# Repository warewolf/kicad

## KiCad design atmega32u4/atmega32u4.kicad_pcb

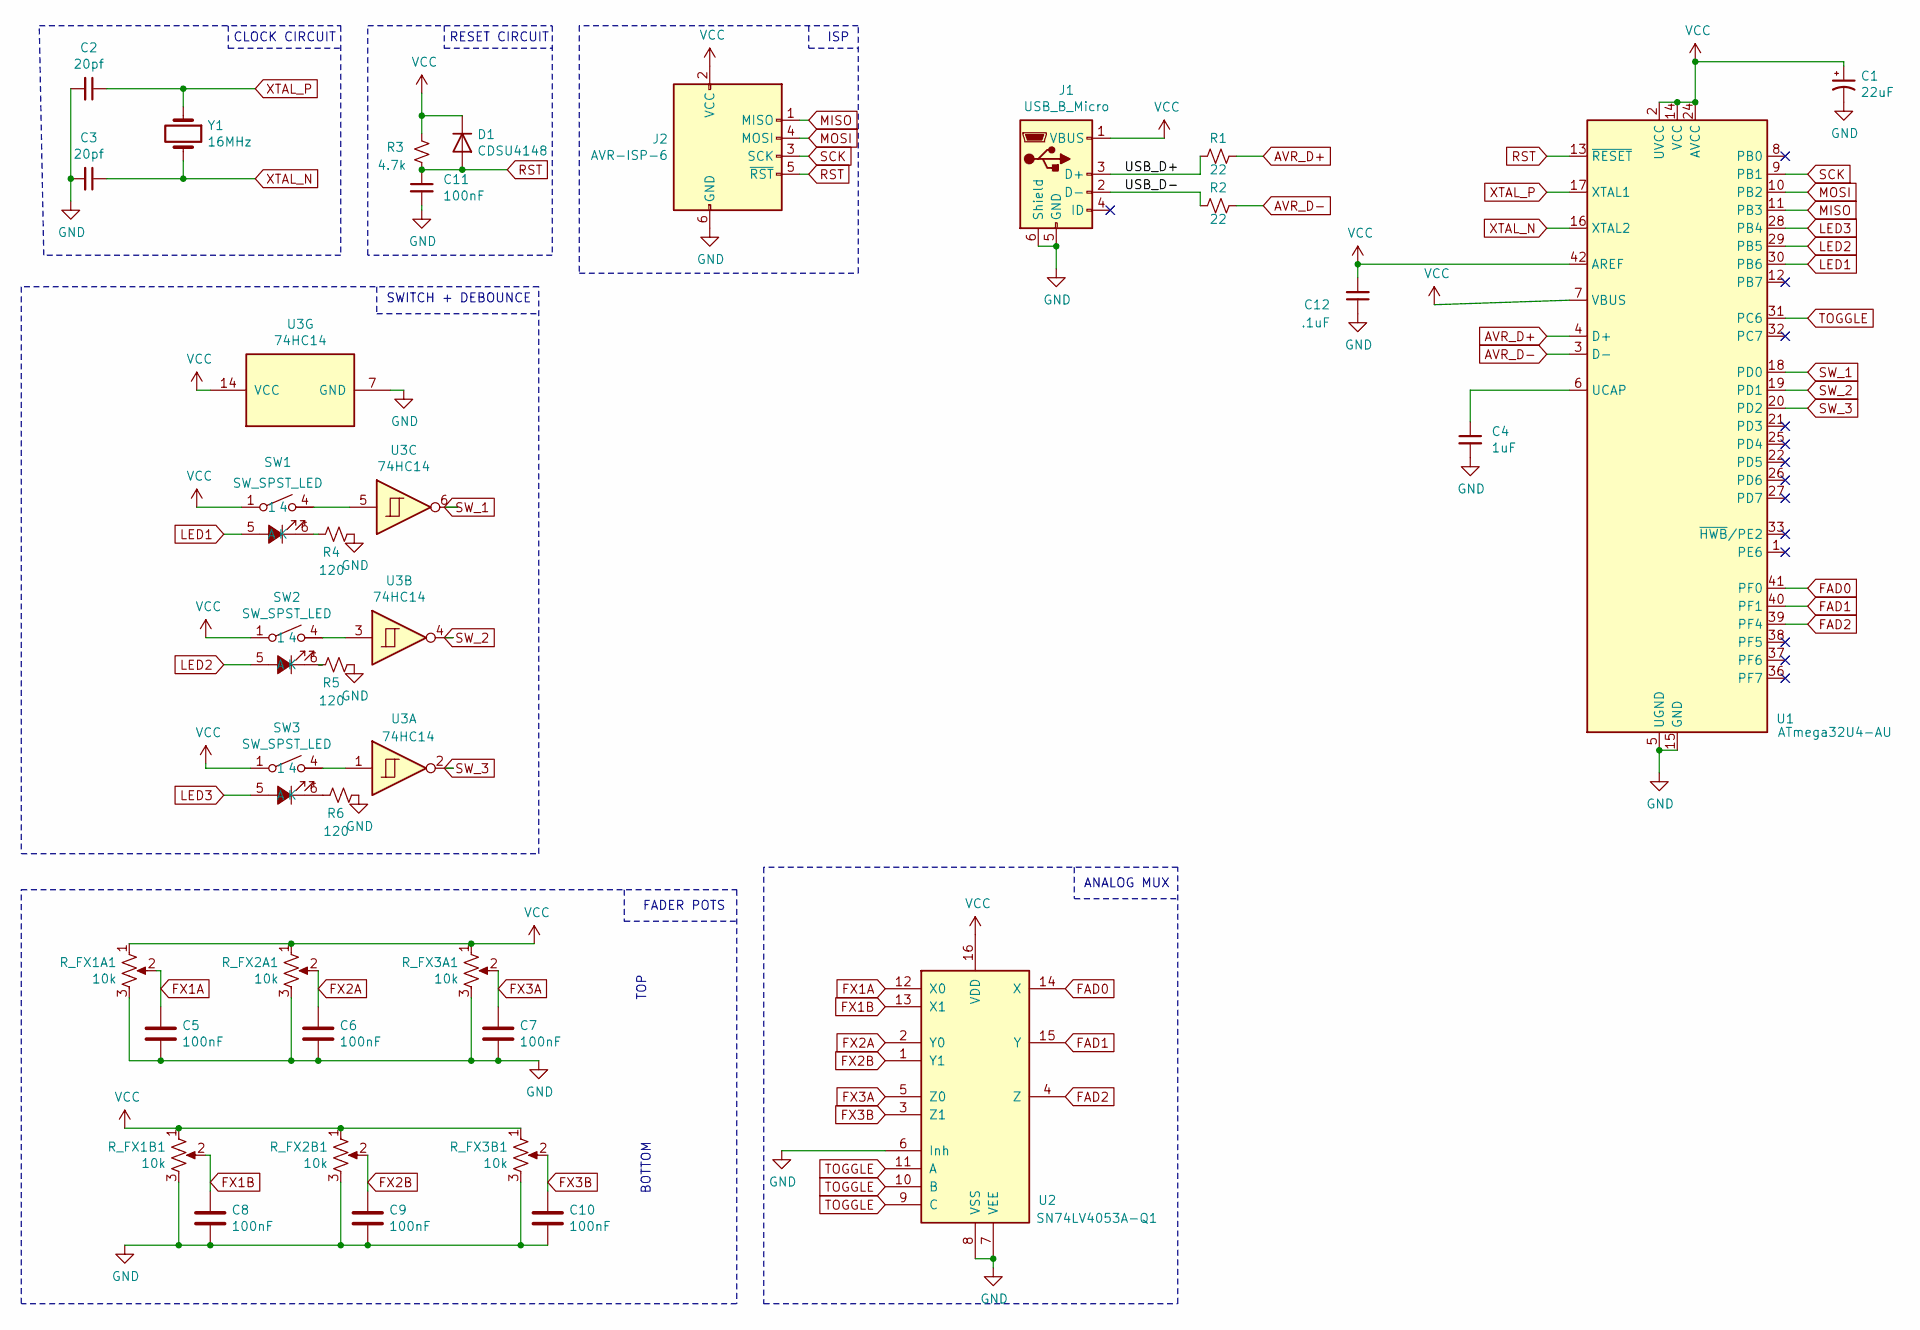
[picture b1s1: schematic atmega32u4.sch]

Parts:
C1: 22uF; CP_Radial_D4.0mm_P2.00mm
C2, C3: 20pf; C_0805_2012Metric
C4: 1uF; C_0805_2012Metric
C5, C6, C7, C8, C9, C10, C11: 100nF; C_0805_2012Metric
C12: .1uF; C_0805_2012Metric
D1: CDSU4148; D_0603_1608Metric
J1: USB_B_Micro; USB_Micro-B_Molex-105017-0001
J2: AVR-ISP-6; PinHeader_2x03_P2.54mm_Vertical
R1, R2: 22; R_0805_2012Metric
R3: 4.7k; R_0805_2012Metric
R4, R5, R6: 120; R_0805_2012Metric
R_FX1A1, R_FX1B1, R_FX2A1, R_FX2B1, R_FX3A1, R_FX3B1: 10k; Potentiometer_TT_P090S_Vertical
SW1, SW2, SW3: SW_SPST_LED; ILS TA180 10
U1: ATmega32U4-AU; TQFP-44_10x10mm_P0.8mm
U2: SN74LV4053A-Q1; TSSOP-16_4.4x5mm_P0.65mm
U3: 74HC14; TSSOP-16_4.4x5mm_P0.65mm
Y1: 16MHz; Crystal_SMD_7050-2Pin_7.0x5.0mm

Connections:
/USB_D+: J1.3 (D+), R1.2
/USB_D-: J1.2 (D-), R2.2
AVR_D+: R1.1, U1.4 (D+)
AVR_D-: R2.1, U1.3 (D-)
FAD0: U1.41 (PF0), U2.14 (X)
FAD1: U1.40 (PF1), U2.15 (Y)
FAD2: U1.39 (PF4), U2.4 (Z)
FX1A: C5.1, R_FX1A1.2, U2.12 (X0)
FX1B: C8.1, R_FX1B1.2, U2.13 (X1)
FX2A: C6.1, R_FX2A1.2, U2.2 (Y0)
FX2B: C9.1, R_FX2B1.2, U2.1 (Y1)
FX3A: C7.1, R_FX3A1.2, U2.5 (Z0)
FX3B: C10.1, R_FX3B1.2, U2.3 (Z1)
GND: C1.2, C2.2, C3.2, C4.2, C5.2, C6.2, C7.2, C8.2, C9.2, C10.2, C11.2, C12.1, J1.5 (GND), J1.6 (Shield), J2.6 (GND), R4.1, R5.1, R6.1, R_FX1A1.3, R_FX1B1.3, R_FX2A1.3, R_FX2B1.3, R_FX3A1.3, R_FX3B1.3, U1.5 (UGND), U1.15 (GND), U1.23 (GND), U1.35 (GND), U1.43 (GND), U2.6 (Inh), U2.7 (VEE), U2.8 (VSS), U3.7 (GND)
LED1: SW1.5 (A), U1.30 (PB6)
LED2: SW2.5 (A), U1.29 (PB5)
LED3: SW3.5 (A), U1.28 (PB4)
MISO: J2.1 (MISO), U1.11 (PB3)
MOSI: J2.4 (MOSI), U1.10 (PB2)
unnamed: C4.1, U1.6 (UCAP)
unnamed: R4.2, SW1.6 (K)
unnamed: R5.2, SW2.6 (K)
unnamed: R6.2, SW3.6 (K)
unnamed: SW1.3, SW1.4, U3.5
unnamed: SW2.3, SW2.4, U3.3
unnamed: SW3.3, SW3.4, U3.1
RST: C11.1, D1.2 (A), J2.5 (~RST), R3.1, U1.13 (~RESET)
SCK: J2.3 (SCK), U1.9 (PB1)
SW_1: U1.18 (PD0), U3.6
SW_2: U1.19 (PD1), U3.4
SW_3: U1.20 (PD2), U3.2
TOGGLE: U1.31 (PC6), U2.9 (C), U2.10 (B), U2.11 (A)
VCC: C1.1, C12.2, D1.1 (K), J1.1 (VBUS), J2.2 (VCC), R3.2, R_FX1A1.1, R_FX1B1.1, R_FX2A1.1, R_FX2B1.1, R_FX3A1.1, R_FX3B1.1, SW1.1, SW1.2, SW2.1, SW2.2, SW3.1, SW3.2, U1.2 (UVCC), U1.7 (VBUS), U1.14 (VCC), U1.24 (AVCC), U1.34 (VCC), U1.42 (AREF), U1.44 (AVCC), U2.16 (VDD), U3.14 (VCC)
XTAL_N: C3.1, U1.16 (XTAL2), Y1.2
XTAL_P: C2.1, U1.17 (XTAL1), Y1.1

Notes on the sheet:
RESET CIRCUIT
BOTTOM
FADER POTS
CLOCK CIRCUIT
SWITCH + DEBOUNCE
TOP
ISP
ANALOG MUX

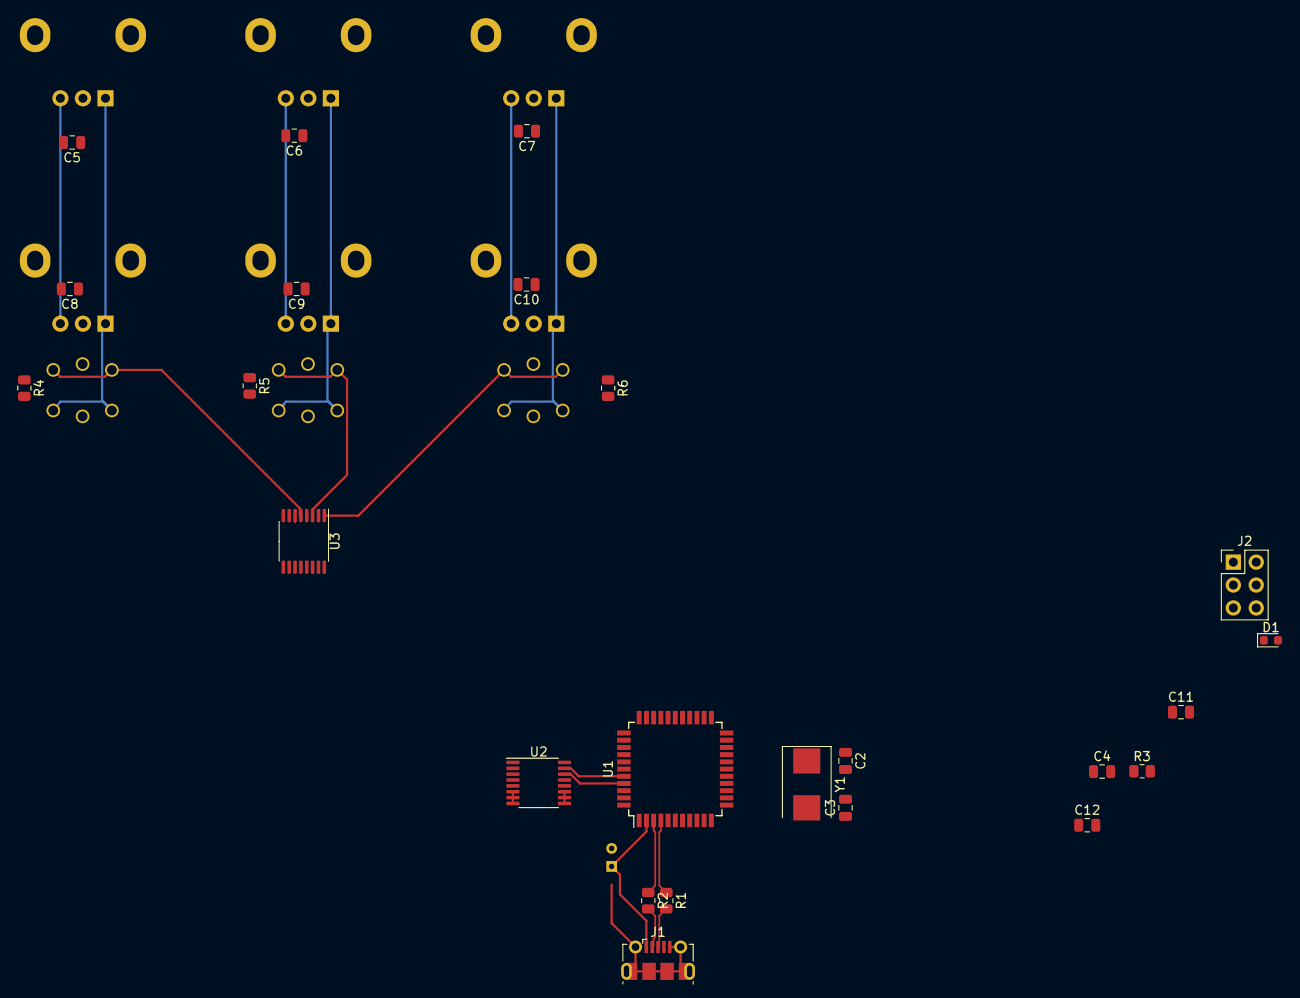
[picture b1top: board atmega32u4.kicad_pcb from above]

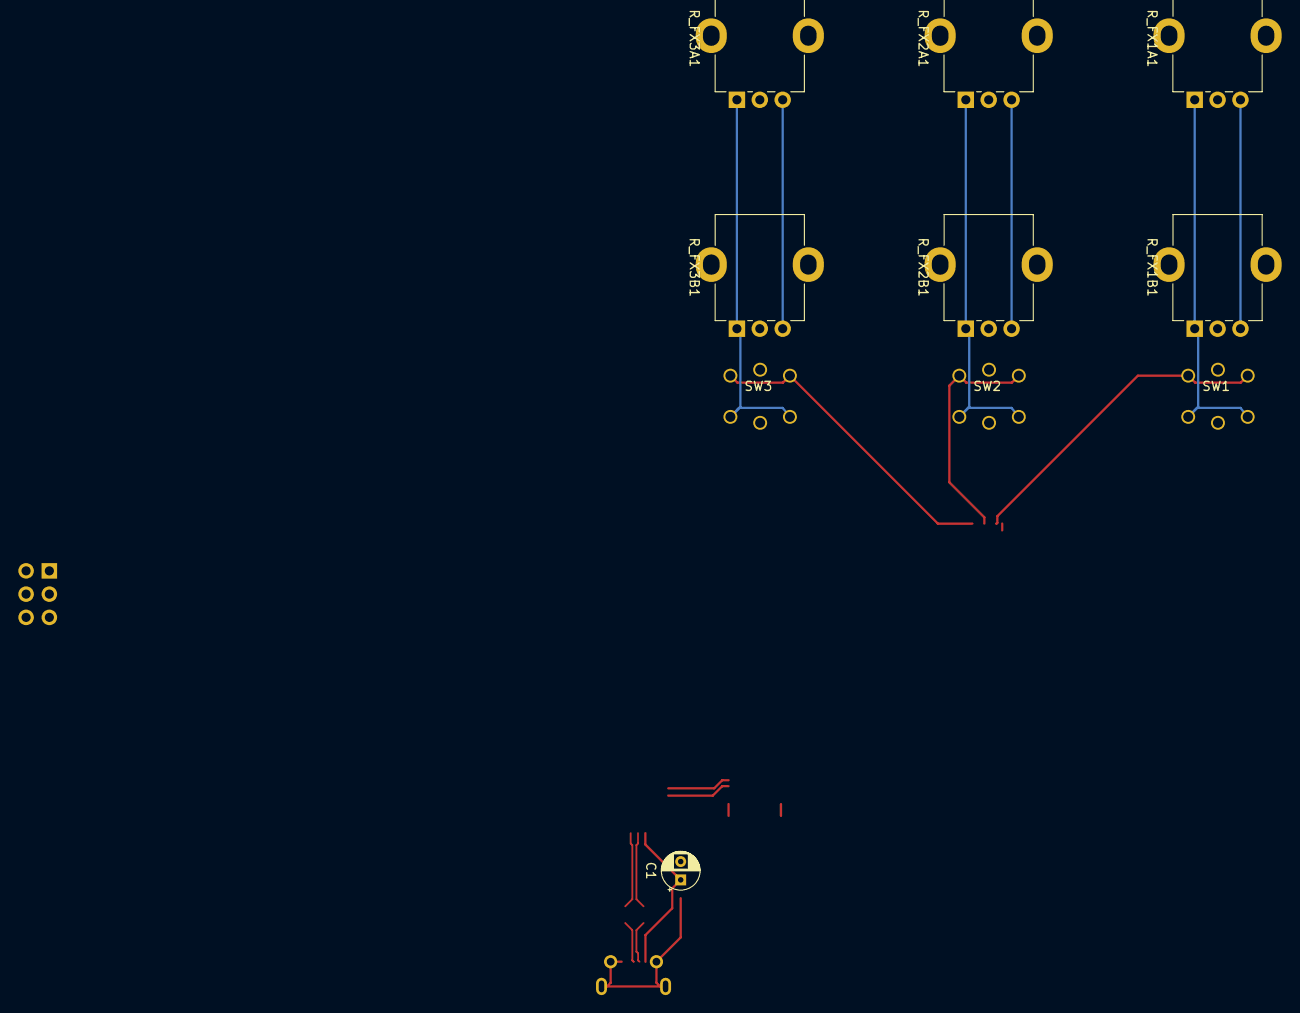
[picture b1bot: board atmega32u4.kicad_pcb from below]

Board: 2 copper layers, 34 parts (10 on the bottom side), 35 nets.

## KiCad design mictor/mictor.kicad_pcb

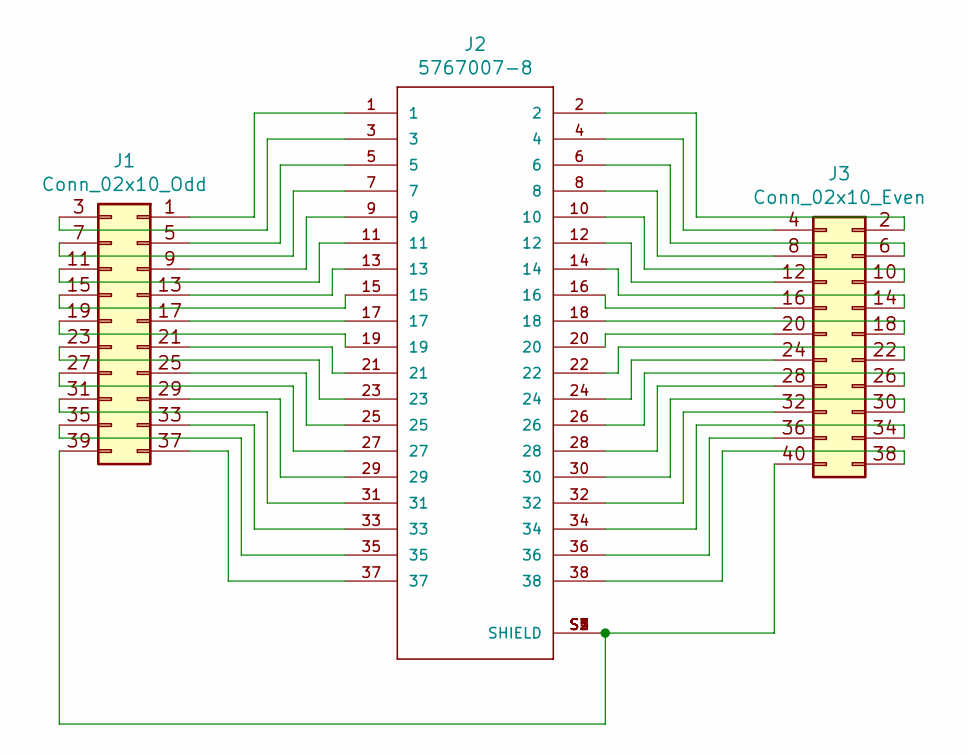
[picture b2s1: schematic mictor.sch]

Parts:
J1: Conn_02x10_Odd; PinHeader_2x10_P2.54mm_Vertical_Odd
J2: 5767007-8; TE_5767007-8
J3: Conn_02x10_Even; PinHeader_2x10_P2.54mm_Vertical_Even

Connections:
unnamed: J1.1, J2.1
unnamed: J1.3, J2.3
unnamed: J1.5, J2.5
unnamed: J1.7, J2.7
unnamed: J1.9, J2.9
unnamed: J1.11, J2.11
unnamed: J1.13, J2.13
unnamed: J1.15, J2.15
unnamed: J1.17, J2.17
unnamed: J1.19, J2.19
unnamed: J1.21, J2.21
unnamed: J1.23, J2.23
unnamed: J1.25, J2.25
unnamed: J1.27, J2.27
unnamed: J1.29, J2.29
unnamed: J1.31, J2.31
unnamed: J1.33, J2.33
unnamed: J1.35, J2.35
unnamed: J1.37, J2.37
unnamed: J1.39, J2.S1 (SHIELD), J2.S2 (SHIELD), J2.S3 (SHIELD), J2.S4 (SHIELD), J2.S5 (SHIELD), J3.40
unnamed: J2.2, J3.2
unnamed: J2.4, J3.4
unnamed: J2.6, J3.6
unnamed: J2.8, J3.8
unnamed: J2.10, J3.10
unnamed: J2.12, J3.12
unnamed: J2.14, J3.14
unnamed: J2.16, J3.16
unnamed: J2.18, J3.18
unnamed: J2.20, J3.20
unnamed: J2.22, J3.22
unnamed: J2.24, J3.24
unnamed: J2.26, J3.26
unnamed: J2.28, J3.28
unnamed: J2.30, J3.30
unnamed: J2.32, J3.32
unnamed: J2.34, J3.34
unnamed: J2.36, J3.36
unnamed: J2.38, J3.38

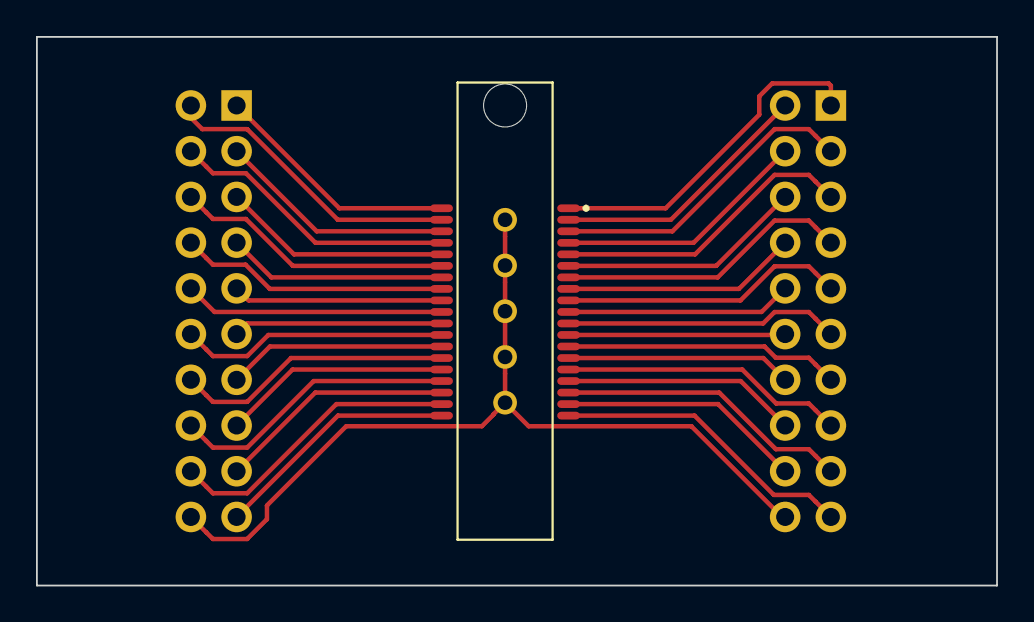
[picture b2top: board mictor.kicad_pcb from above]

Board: 2 copper layers, 53.3 x 30.5 mm, 3 parts (0 on the bottom side), 39 nets.

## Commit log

2019-03-23 Add mictor 38 breakout
    Available on OshPark https://oshpark.com/shared_projects/s0vMc2Jp
2019-04-02 WIP on wo-33a
2019-04-02 Add svg readme mojo
2019-04-02 fixies?
2019-04-02 Make readme more descriptive
2019-04-03 moar work
2022-03-19 Add rmpogo
2022-03-19 this is better, me thinks
